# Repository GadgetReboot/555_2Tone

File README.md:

# 555_2Tone
Simple 555 warble tone generator

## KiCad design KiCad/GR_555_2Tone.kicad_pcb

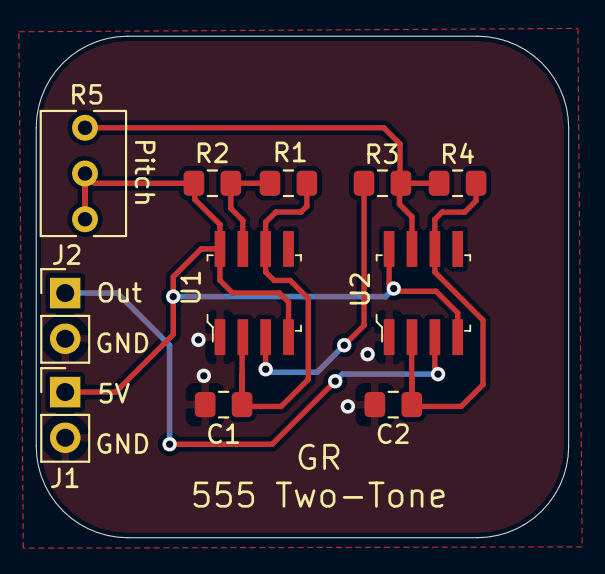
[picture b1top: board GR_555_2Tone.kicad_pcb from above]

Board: 2 copper layers, 29.6 x 27.9 mm, 11 parts (0 on the bottom side), 8 nets.

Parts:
C1, C2: 100nF; C_0805_2012Metric_Pad1.15x1.40mm_HandSolder
J1, J2: Conn_01x02; PinHeader_1x02_P2.54mm_Vertical
R1, R3: 510K; R_0805_2012Metric_Pad1.15x1.40mm_HandSolder
R2, R4: 10K; R_0805_2012Metric_Pad1.15x1.40mm_HandSolder
R5: 10K; Potentiometer_Bourns_3266Y_Vertical
U1, U2: NE555DR; SOIC-8_W3.9mm

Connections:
+5V: J1.1, R2.1, R5.1, R5.2, U1.4, U1.8, U2.4, U2.8
/Disch1: R1.2, R2.2, U1.7
/Disch2: R3.1, R4.2, R5.3, U2.7
GNDREF: C1.2, C2.2, J1.2, J2.2, U1.1, U2.1
unnamed: C1.1, R1.1, U1.2, U1.6
unnamed: C2.1, R4.1, U2.2, U2.6
unnamed: J2.1, U2.3
unnamed: R3.2, U1.3
